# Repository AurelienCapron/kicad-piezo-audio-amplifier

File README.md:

# Chaîne d'Amplification Audio Piézoélectrique & PCB CMS (KiCad 9)

Conception, simulation SPICE, routage PCB en composants montés en surface (CMS) et caractérisation expérimentale d'une chaîne complète de conditionnement et d'amplification audio pour capteur piézoélectrique (guitare acoustique, contrebasse). Le système est alimenté en asymétrique (0V/5V) et réparti sur deux cartes électroniques : une première dédiée à la préamplification et à l'égalisation active (filtre de Baxandall), et une seconde intégrant une correction physiologique (*Loudness*) ainsi que deux étages de puissance sélectionnables (Classe AB et Classe D) pour piloter un haut-parleur de 8 Ω (2 W).

* **[Consulter le rapport complet de caractérisation et fiches de mesures (PDF)](docs/characterization_report.pdf)**

---

## Sommaire
1. [Architecture globale et cartes PCB réalisées](#architecture-globale-et-cartes-pcb-réalisées)
2. [Structure du dépôt](#structure-du-dépôt)
3. [Conception électronique détaillée (Cartes 1 et 2)](#conception-électronique-détaillée-cartes-1-et-2)
4. [Caractérisation expérimentale et résultats](#caractérisation-expérimentale-et-résultats)
5. [Nomenclature des composants principaux (BOM)](#nomenclature-des-composants-principaux-bom)
6. [Ouverture des fichiers de conception (KiCad 9)](#ouverture-des-fichiers-de-conception-kicad-9)

---

## Architecture globale et cartes PCB réalisées

| Carte PCB 1 soudée (Préampli, Baxandall & Alim 5V) | Carte PCB 2 soudée (Loudness, Classe AB & Classe D) |
| :---: | :---: |
|  |  |
| *AOP ST TSV912IDT (SOIC-8), régulateur LDO 5V (SOT-223) et potentiomètres Vishay TS53YL* | *Ampli Classe AB TS4871 (SOIC-8), Ampli Classe D TS4962 (DFN-8) et cavalier de sélection* |

---

## Structure du dépôt

```text
kicad-piezo-audio-amplifier/
├── .gitignore
├── README.md
├── assets/
│   ├── audio_chain_architecture.svg  # Schéma synoptique vectoriel des 2 cartes PCB
│   ├── baxandall_bode_boost.png      # Diagramme de Bode expérimental (Modes Boost)
│   ├── baxandall_bode_cut.png        # Diagramme de Bode expérimental (Modes Cut)
│   ├── baxandall_schematic.png       # Schéma KiCad du filtre actif de Baxandall
│   ├── class_d_pwm_envelope.png      # Capture Tektronix : signal audio 300 Hz et enveloppe PWM
│   ├── class_d_pwm_zoom_neg.png      # Capture Tektronix : découpage PWM sur alternance négative
│   ├── class_d_pwm_zoom_pos.png      # Capture Tektronix : découpage PWM sur alternance positive
│   ├── pcb_part1_preamp.png          # Carte PCB 1 soudée en CMS
│   └── pcb_part2_power_amp.png       # Carte PCB 2 soudée en CMS
├── docs/
│   └── characterization_report.pdf   # Fiches de mesures complètes (Baxandall & Classe D)
└── hardware_kicad/
    ├── BE-Elec-S2.kicad_pro          # Fichier de projet KiCad 9.0
    ├── BE-Elec-S2.kicad_sch          # Schéma racine hiérarchique
    ├── Partie-1.kicad_sch            # Schéma Carte 1 (Préampli, Baxandall, Volume, Alim)
    ├── Partie-2.kicad_sch            # Schéma Carte 2 (Loudness, Ampli Classe AB & Classe D)
    └── BE-Elec-S2.kicad_pcb          # Routage PCB complet (empreintes CMS 1206, SOIC-8, DFN-8)
```

---

## Conception électronique détaillée (Cartes 1 et 2)

### 1. Carte PCB 1 : Alimentation, Préamplification et Égaliseur de Baxandall
La première carte assure l'adaptation d'impédance du disque piézoélectrique et la mise en forme spectrale du signal avec une excursion maximale de sortie de $5\text{ V}_{\text{pp}}$ :
* **Régulation 5V et masse virtuelle ($V_{\text{ref}} = 2,5\text{ V}$) :** Un régulateur LDO `TLV1117-50` (`LD1117`, boîtier SOT-223) abaisse la tension d'entrée 12V vers un rail régulé `VCC = 5V`. L'alimentation étant asymétrique (0V/5V), une polarisation à $V_{\text{ref}} = \text{VCC}/2 = 2,5\text{ V}$ est générée par ponts diviseurs (`R1`/`R2` de $100\text{ k}\Omega$ et `R3`/`R4` de $10\text{ k}\Omega$) pour centrer le signal audio et éviter tout écrêtage des alternances négatives.
* **Étage suiveur et préamplificateur (`U1` — ST `TSV912IDT`) :** Le signal issu du capteur piézoélectrique traverse un condensateur de couplage (`C1 = 1 µF`), passe par un amplificateur opérationnel monté en suiveur (`U1A`) offrant une haute impédance d'entrée, puis est amplifié par un montage inverseur (`U1B`, `R5 = 10 kΩ`, `R6 = 100 kΩ`) fixant un gain en tension de $\vert{}A_v\vert{} = R_6 / R_5 = 10$ (+20 dB).
* **Correcteur de tonalité actif de Baxandall (`U2A` — ST `TSV912IDT`) :** Réseau actif RC et potentiométrique permettant un réglage indépendant des graves et des aigus autour d'une fréquence charnière fixée à **1 kHz** :
  * **Voie Graves (Bass) :** Potentiomètre `RV1 = 50 kΩ`, résistances `RB1 = RB2 = 15 kΩ` et condensateurs `CB1 = CB2 = 33 nF`.
  * **Voie Aigus (Treble) :** Potentiomètre `RV2 = 50 kΩ`, résistances `RT1 = RT2 = 3,3 kΩ` et condensateurs `CT1 = CT2 = 3,3 nF`.

* **Contrôle de volume actif (`U2B` — ST `TSV912IDT`) :** Montage inverseur à gain variable (`R7 = 10 kΩ` en entrée et potentiomètre `RV3 = 50 kΩ` en contre-réaction) permettant d'ajuster le niveau injecté vers la carte de puissance.

### 2. Carte PCB 2 : Correcteur Loudness et Amplification Classe AB / Classe D
* **Correcteur physiologique (*Loudness*) :** Filtre passif RC associé au potentiomètre `RV5 = 10 kΩ` (`R10 = 120 Ω`, `R11 = 10 kΩ`, `C9 = 15 µF`, `C10 = 180 pF`) compensant la perte de sensibilité de l'oreille humaine aux extrémités du spectre sonore (basses et hautes fréquences) à faible volume d'écoute.
* **Amplificateur de puissance Classe AB (`U_AB1` — ST `TS4871IDT`) :** Amplificateur audio linéaire Rail-to-Rail 1 W en boîtier SOIC-8 configuré avec une résistance d'entrée `Rin1 = 22 kΩ` et une contre-réaction `Rfeed1 = 22 kΩ` (`Cfeed1 = 330 pF`).
* **Amplificateur de puissance Classe D (`U_D1` — ST `TS4962`) :** Amplificateur à découpage PWM sans filtre de sortie (*filter-free*) en boîtier miniature `DFN-8` ($3\times3\text{ mm}$). Avec une résistance de contre-réaction interne $R_f = 150\text{ k}\Omega$ et des composants d'entrée $R_8 = R_9 = 150\text{ k}\Omega$ et $C_{s2} = C_{s3} = 100\text{ nF}$, la fréquence de coupure basse et le gain différentiel théorique en topologie pontée (**BTL — Bridge-Tied Load**) valent :

$$f_c = \frac{1}{2\pi R_{\text{in}} C_{\text{in}}} = \frac{1}{2\pi \times 150\times 10^3 \times 100\times 10^{-9}} \approx 10,6\text{ Hz}$$

$$A_v = 2 \times \frac{R_f}{R_{\text{in}}} = 2 \times \frac{150\text{ k}\Omega}{150\text{ k}\Omega} = 2 \quad (+6,02\text{ dB})$$

---

## Caractérisation expérimentale et résultats

Les campagnes de validation ont été réalisées à l'aide d'un générateur de fonctions **GW Instek AFG-2112** et d'un oscilloscope numérique **Tektronix TBS 1052B-EDU**.

### 1. Réponse fréquentielle du filtre de Baxandall (1 Hz – 20 kHz)
Sept configurations des potentiomètres `RV1` (Graves) et `RV2` (Aigus) ont été caractérisées sur banc d'essai avec un signal sinusoïdal d'entrée $V_e = 100\text{ mV}$ :

| Configuration | Position Graves (`RV1`) | Position Aigus (`RV2`) | Gain Graves mesuré | Gain Aigus mesuré | Fréquence de coupure / pivot (-3 dB) |
|---|---|---|---|---|---|
| **1. Neutre (Suiveur)** | 50 % | 50 % | `0,0 dB` | `0,0 dB` | Réponse plate sur `[10 Hz – 20 kHz]` |
| **2. Bass Boost** | 100 % | 50 % | **`+12,6 dB`** | `0,0 dB` | $f_c \approx 100\text{ Hz}$ |
| **3. Treble Boost** | 50 % | 100 % | `0,0 dB` | **`+11,2 dB`** | $f_c \approx 4\text{ kHz}$ |
| **4. Dual Boost** | 100 % | 100 % | **`+12,6 dB`** | **`+11,2 dB`** | Fréquence charnière centrée à `1 kHz (0 dB)` |
| **5. Bass Cut** | 0 % | 50 % | **`-13,0 dB`** | `0,0 dB` | $f_c \approx 300\text{ Hz}$ |
| **6. Treble Cut** | 50 % | 0 % | `0,0 dB` | **`-11,2 dB`** | $f_c \approx 4\text{ kHz}$ |
| **7. Dual Cut** | 0 % | 0 % | **`-13,0 dB`** | **`-11,2 dB`** | Sommet résiduel à `1 kHz (~0 dB)` |

| Réponse fréquentielle en amplification (Boost) | Réponse fréquentielle en atténuation (Cut) |
| :---: | :---: |
|  |  |

### 2. Caractérisation PWM et mesure différentielle BTL de l'amplificateur Classe D (`TS4962`)
La sortie de l'amplificateur `TS4962` étant pontée (BTL), aucune des deux bornes `OUT+` et `OUT-` ne doit être reliée à la masse de l'oscilloscope sous peine de court-circuiter un demi-pont. La caractérisation a donc été effectuée en mode mathématique différentiel (**`CH2 - CH3`**) avec un signal test à $300\text{ Hz}$ :

| Grandeur caractérisée | Valeur théorique | Valeur expérimentale | Incertitude | Unité |
|---|---|---|---|---|
| Tension d'entrée crête-à-crête ($V_{\text{in}}$) | `280` | **`280`** | $\pm 0,1$ | mV |
| Tension de sortie différentielle BTL ($V_{\text{out}}$) | `560` | **`548`** | $\pm 20$ | mV |
| Gain en tension mesuré ($A_v = V_{\text{out}} / V_{\text{in}}$) | `2,00` | **`1,96`** | $\pm 0,15$ | — |
| Amplitude des créneaux de découpage ($V_{\text{pwm}}$) | `5,00` | **`4,88`** | $\pm 0,10$ | V |
| Fréquence de découpage PWM ($f_{\text{sw}}$) | `250 – 300` | **`266`** | $\pm 15$ | kHz |
| Rapport cyclique au repos ($DC_{\text{repos}}$) | `50,0` | **`50,4`** | $\pm 2,0$ | % |
| Excursion du rapport cyclique ($DC_{\text{min}}$ / $DC_{\text{max}}$) | `< 50` / `> 50` | **`40` / `60`** | $\pm 2,0$ | % |

| Enveloppe PWM globale ($2,50\text{ ms/div}$) | Découpage PWM sur creux négatif ($2,50\ \mu\text{s/div}$) | Découpage PWM sur pic positif ($2,50\ \mu\text{s/div}$) |
| :---: | :---: | :---: |
|  |  |  |
| *Entrée sinusoïdale 300 Hz ($280\text{ mV}_{\text{pp}}$) et découpage BTL* | *Rapport cyclique réduit ($DC_{\text{min}} \approx 40\ \%$)* | *Rapport cyclique élargi ($DC_{\text{max}} \approx 60\ \%$)* |

---

## Nomenclature des composants principaux (BOM)

| Référence | Composant | Fabricant | Boîtier CMS | Fonction |
|---|---|---|---|---|
| **`U1`, `U2`** | `TSV912IDT` | STMicroelectronics | `SOIC-8` | Doubles AOP Rail-to-Rail 8 MHz (Suiveur, Préampli, Baxandall, Volume) |
| **`U_AB1`** | `TS4871IDT` | STMicroelectronics | `SOIC-8` | Amplificateur de puissance audio Classe AB (1 W, BTL, Standby) |
| **`U_D1`** | `TS4962` | STMicroelectronics | `DFN-8` ($3\times3\text{ mm}$) | Amplificateur de puissance audio Classe D sans filtre (2,8 W, PWM 266 kHz) |
| **`U3`** | `TLV1117-50` / `LD1117` | ST / Texas Instruments | `SOT-223` | Régulateur linéaire LDO fixe 5,0 V (800 mA) |
| **`RV1`–`RV3`, `RV5`** | `TS53YL` (50 kΩ / 10 kΩ) | Vishay | CMS Vertical | Potentiomètres cermet (Graves, Aigus, Volume, Loudness) |
| **Passifs `R` / `C`** | Série E6 (`1206`) | Divers | `1206` (3216 Metric) | Résistances, condensateurs céramiques et électrolytiques CMS ($6,3\times5,2\text{ mm}$) |

---

## Ouverture des fichiers de conception (KiCad 9)

1. Installer **KiCad 9.0** (ou version ultérieure).
2. Ouvrir le projet `hardware_kicad/BE-Elec-S2.kicad_pro`.
3. Naviguer dans les deux sous-feuilles hiérarchiques `Partie-1.kicad_sch` et `Partie-2.kicad_sch` depuis l'éditeur de schémas (`eeschema`), ou ouvrir `BE-Elec-S2.kicad_pcb` dans l'éditeur de circuit imprimé (`pcbnew`).

---

## Auteurs

Projet réalisé en binôme par **Aurélien Capron** et **Amaury Simonnot** au sein de **Grenoble INP - Phelma** (Filière Systèmes Électroniques Intégrés / Tronc commun 1A).

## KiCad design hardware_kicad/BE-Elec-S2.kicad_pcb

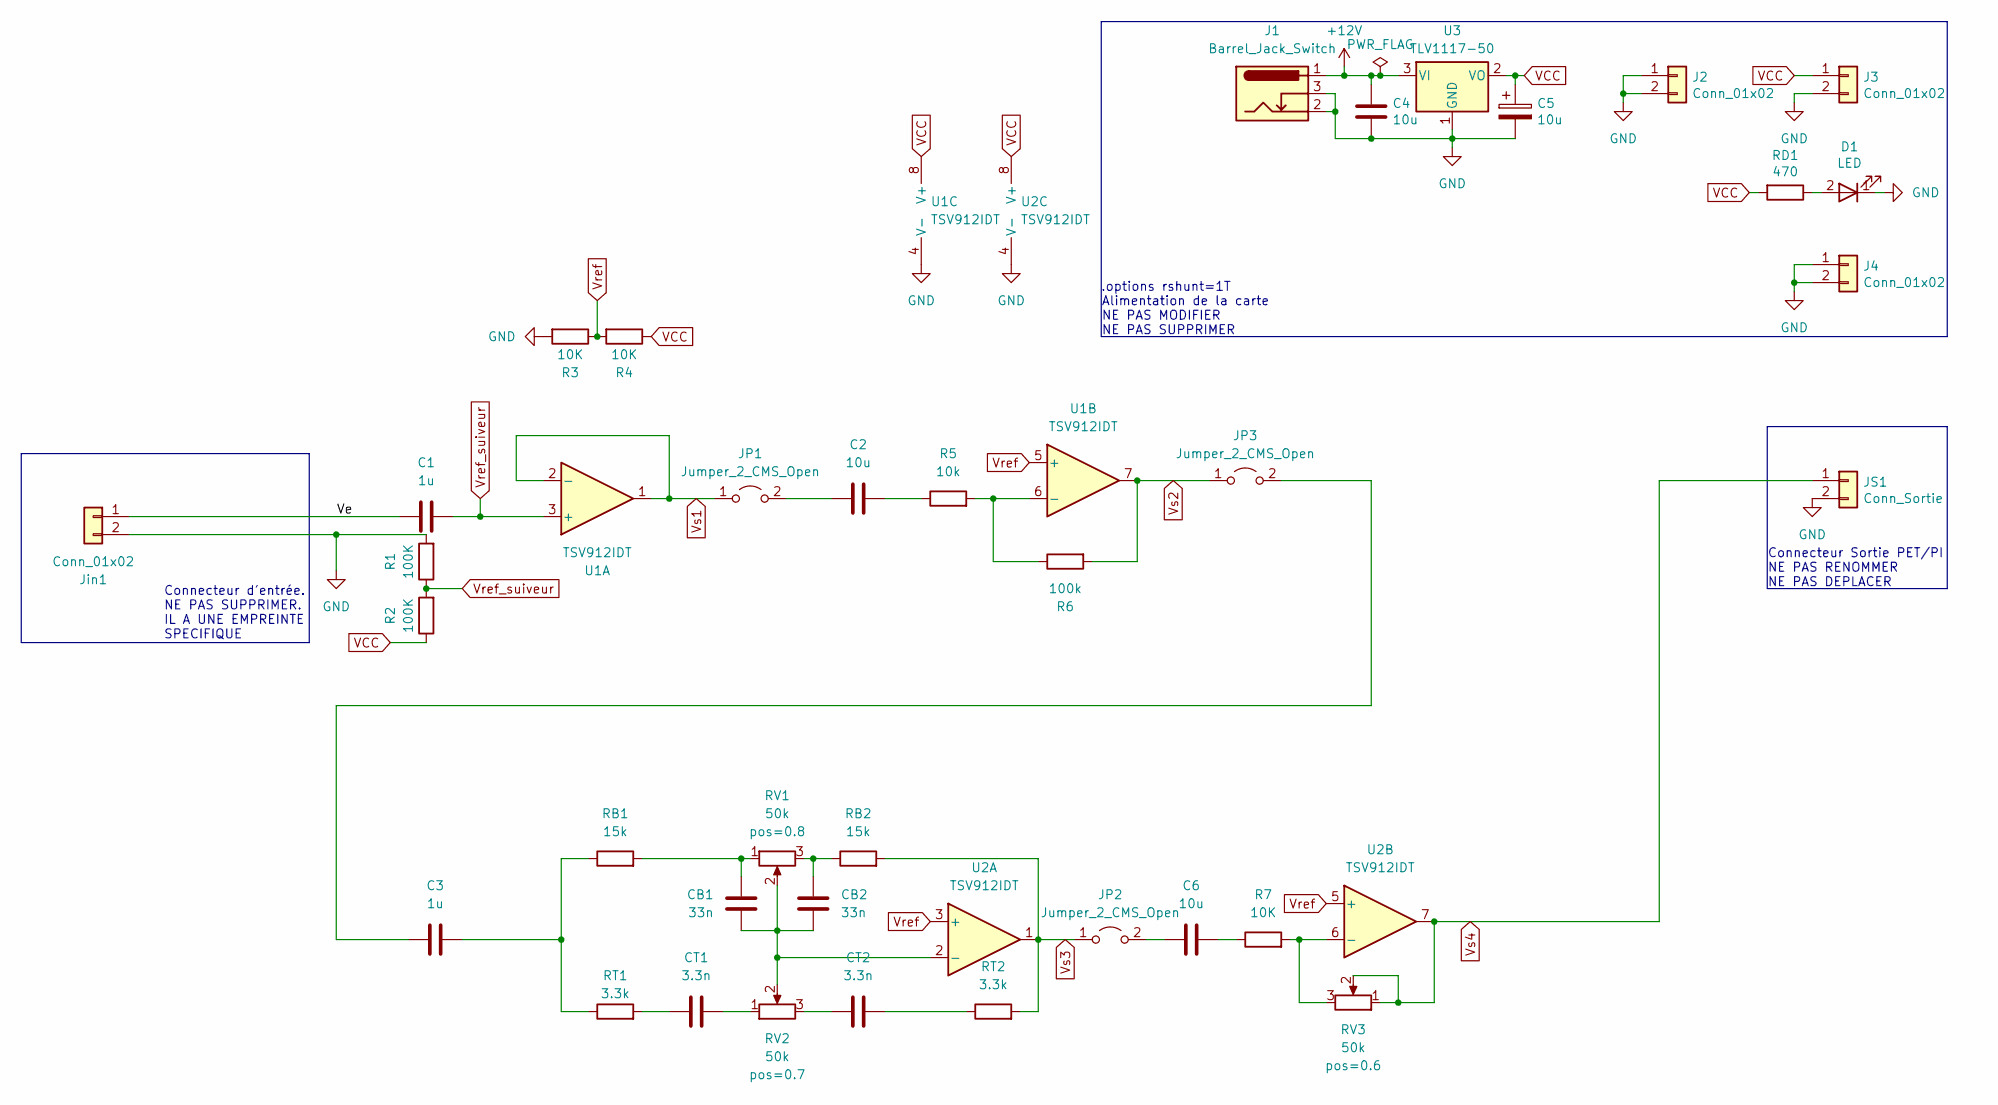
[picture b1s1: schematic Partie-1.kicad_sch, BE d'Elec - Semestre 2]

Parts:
C1, C3: 1u; C_1206_3216Metric_Pad1.42x1.75mm_HandSolder
C2, C4, C6: 10u; C_1206_3216Metric_Pad1.42x1.75mm_HandSolder
C5: 10u; CP_Elec_6.3x5.2
CB1, CB2: 33n; C_1206_3216Metric_Pad1.42x1.75mm_HandSolder
CT1, CT2: 3.3n; C_1206_3216Metric_Pad1.42x1.75mm_HandSolder
D1: LED; LED_1206_3216Metric_Pad1.42x1.75mm_HandSolder
J1: Barrel_Jack_Switch; BarrelJack_CLIFF_FC681465S_SMT_Horizontal
J2, J3, J4: Conn_01x02; PinHeader_1x02_P2.54mm_Vertical
JP1, JP2, JP3: Jumper_2_CMS_Open; SolderJumper-2_P1.3mm_Open_TrianglePad1.0x1.5mm
JS1: Conn_Sortie; PinHeader_1x02_P2.54mm_Vertical
Jin1: Conn_01x02; PinHeader_1x02_P2.54mm_Vertical
R1, R2: 100K; R_1206_3216Metric_Pad1.42x1.75mm_HandSolder
R3, R4, R7: 10K; R_1206_3216Metric_Pad1.42x1.75mm_HandSolder
R5: 10k; R_1206_3216Metric_Pad1.42x1.75mm_HandSolder
R6: 100k; R_1206_3216Metric_Pad1.42x1.75mm_HandSolder
RB1, RB2: 15k; R_1206_3216Metric_Pad1.42x1.75mm_HandSolder
RD1: 470; R_1206_3216Metric_Pad1.42x1.75mm_HandSolder
RT1, RT2: 3.3k; R_1206_3216Metric_Pad1.42x1.75mm_HandSolder
RV1, RV2, RV3: 50k; Potentiometer_Vishay_TS53YL_Vertical
U1, U2: TSV912IDT; SOIC-8_3.9x4.9mm_P1.27mm
U3: TLV1117-50; SOT-223-3_TabPin2

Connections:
+12V: C4.1, J1.1, U3.3 (VI)
/Partie-1/Ve: C1.1, Jin1.1
GND: C4.2, C5.2, D1.1 (K), J1.2, J1.3, J2.1, J2.2, J3.2, J4.1, J4.2, JS1.2, Jin1.2, R1.2, R3.2, U1.4 (V-), U2.4 (V-), U3.1 (GND); also elsewhere on the board
unnamed: C2.2, R5.1
unnamed: C3.2, RB1.1, RT1.1
unnamed: C6.2, R7.1
unnamed: CB1.2, RB1.2, RV1.1
unnamed: CB2.2, RB2.1, RV1.3
unnamed: CT1.1, RT1.2
unnamed: CT1.2, RV2.1
unnamed: CT2.1, RV2.3
unnamed: CT2.2, RT2.1
unnamed: D1.2 (A), RD1.1
unnamed: C2.1, JP1.2 (B)
unnamed: C6.1, JP2.2 (B)
unnamed: C3.1, JP3.2 (B)
unnamed: R5.2, R6.1, U1.6 (-)
unnamed: CB1.1, CB2.1, RV1.2, RV2.2, U2.2 (-)
unnamed: R7.2, RV3.3, U2.6 (-)
VCC: C5.1, J3.1, R2.1, R4.1, RD1.2, U1.8 (V+), U2.8 (V+), U3.2 (VO); also elsewhere on the board
Vref: R3.1, R4.2, U1.5 (+), U2.3 (+), U2.5 (+)
Vref_suiveur: C1.2, R1.1, R2.2, U1.3 (+)
Vs1: JP1.1 (A), U1.1, U1.2 (-)
Vs2: JP3.1 (A), R6.2, U1.7
Vs3: JP2.1 (A), RB2.2, RT2.2, U2.1
Vs4: JS1.1, RV3.1, RV3.2, U2.7

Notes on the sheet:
Connecteur d'entrée. NE PAS SUPPRIMER. IL A UNE EMPREINTE SPECIFIQUE
.options rshunt=1T
Connecteur Sortie PET/PI NE PAS RENOMMER NE PAS DEPLACER
Alimentation de la carte NE PAS MODIFIER NE PAS SUPPRIMER

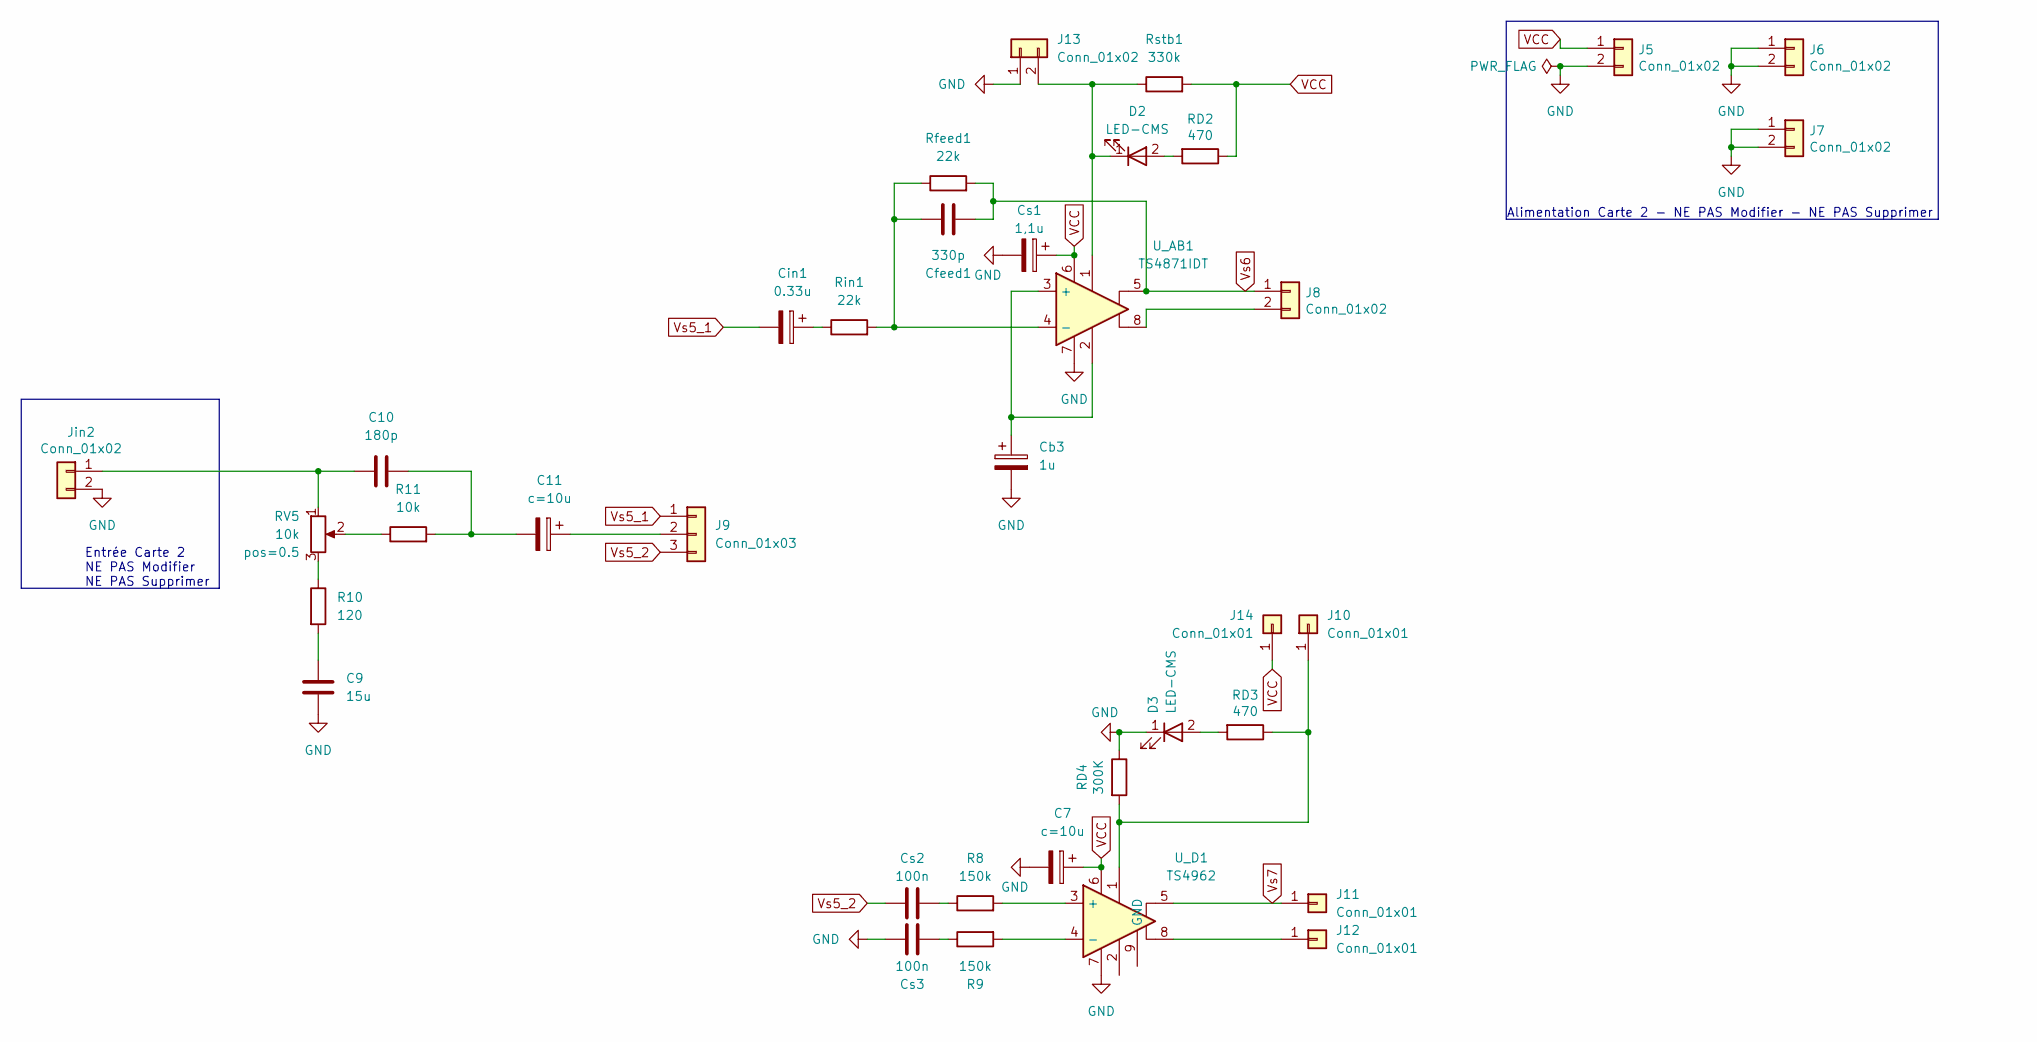
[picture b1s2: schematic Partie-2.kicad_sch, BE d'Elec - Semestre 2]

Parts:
C7, C11: c=10u; CP_Elec_6.3x5.2
C9: 15u; C_1206_3216Metric_Pad1.42x1.75mm_HandSolder
C10: 180p; C_1206_3216Metric_Pad1.42x1.75mm_HandSolder
Cb3: 1u; CP_Elec_6.3x5.2
Cfeed1: 330p; C_1206_3216Metric_Pad1.42x1.75mm_HandSolder
Cin1: 0.33u; CP_Elec_6.3x5.2
Cs1: 1,1u; CP_Elec_6.3x5.2
Cs2, Cs3: 100n; C_1206_3216Metric_Pad1.42x1.75mm_HandSolder
D2, D3: LED-CMS; LED_1206_3216Metric_Pad1.42x1.75mm_HandSolder
J5, J6, J7, J8, J13: Conn_01x02; PinHeader_1x02_P2.54mm_Vertical
J9: Conn_01x03; PinHeader_1x03_P2.54mm_Vertical
J10, J11, J12, J14: Conn_01x01; PinHeader_1x01_P2.54mm_Vertical
Jin2: Conn_01x02; PinHeader_1x02_P2.54mm_Vertical
R8, R9: 150k; R_1206_3216Metric_Pad1.42x1.75mm_HandSolder
R10: 120; R_1206_3216Metric_Pad1.42x1.75mm_HandSolder
R11: 10k; R_1206_3216Metric_Pad1.42x1.75mm_HandSolder
RD2, RD3: 470; R_1206_3216Metric_Pad1.42x1.75mm_HandSolder
RD4: 300K; R_1206_3216Metric_Pad1.42x1.75mm_HandSolder
RV5: 10k; Potentiometer_Vishay_TS53YL_Vertical
Rfeed1: 22k; R_1206_3216Metric_Pad1.42x1.75mm_HandSolder
Rin1: 22k; R_1206_3216Metric_Pad1.42x1.75mm_HandSolder
Rstb1: 330k; R_1206_3216Metric_Pad1.42x1.75mm_HandSolder
U_AB1: TS4871IDT; SOIC-8_3.9x4.9mm_P1.27mm
U_D1: TS4962; DFN-8-1EP_3x3mm_P0.65mm_EP1.55x2.4mm

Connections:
GND: C7.2, C9.1, Cb3.2, Cs1.2, Cs3.1, D3.1 (K), J5.2, J6.1, J6.2, J7.1, J7.2, J13.1, Jin2.2, RD4.1, U_AB1.7, U_D1.7; also elsewhere on the board
unnamed: C9.2, R10.2
unnamed: C10.2, C11.2, R11.2
unnamed: Cin1.1, Rin1.1
unnamed: Cs2.2, R8.1
unnamed: Cs3.2, R9.1
unnamed: D2.2 (A), RD2.2
unnamed: D2.1 (K), J13.2, Rstb1.1, U_AB1.1
unnamed: D3.2 (A), RD3.2
unnamed: J8.2, U_AB1.8
unnamed: C11.1, J9.2
unnamed: J10.1, RD3.1, RD4.2, U_D1.1
unnamed: J12.1, U_D1.8
unnamed: C10.1, Jin2.1, RV5.1
unnamed: R10.1, RV5.3
unnamed: R11.1, RV5.2
unnamed: Cb3.1, U_AB1.2, U_AB1.3 (+)
unnamed: Cfeed1.1, Rfeed1.1, Rin1.2, U_AB1.4 (-)
unnamed: R8.2, U_D1.3 (+)
unnamed: R9.2, U_D1.4 (-)
VCC: C7.1, Cs1.1, J5.1, J14.1, RD2.1, Rstb1.2, U_AB1.6, U_D1.6; also elsewhere on the board
Vs5_1: Cin1.2, J9.1
Vs5_2: Cs2.1, J9.3
Vs6: Cfeed1.2, J8.1, Rfeed1.2, U_AB1.5
Vs7: J11.1, U_D1.5

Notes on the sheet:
Entrée Carte 2 NE PAS Modifier NE PAS Supprimer
Alimentation Carte 2 - NE PAS Modifier - NE PAS Supprimer

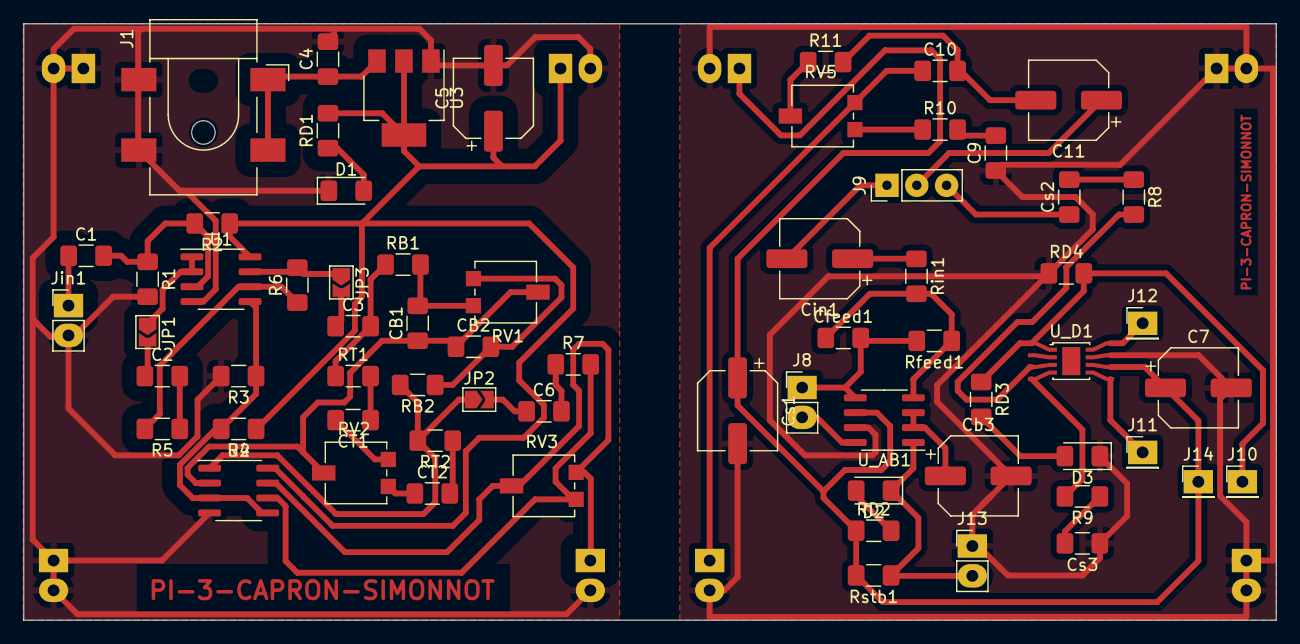
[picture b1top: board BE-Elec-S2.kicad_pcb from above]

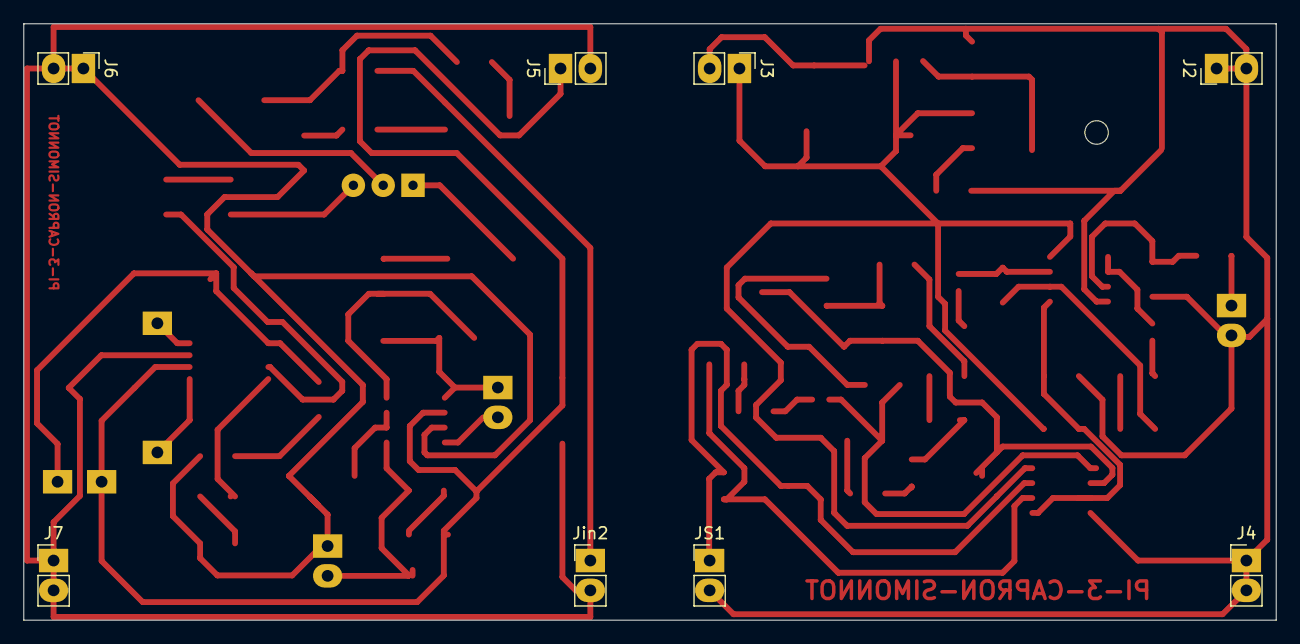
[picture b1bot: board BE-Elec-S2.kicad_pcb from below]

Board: 4 copper layers, 106.7 x 50.8 mm, 74 parts (8 on the bottom side), 49 nets.
